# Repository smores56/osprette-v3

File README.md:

The Osprangle
=============

The Osprangle is a slightly modified version of the [Osprette V3][osprette-v3], fit for a rectangular case.
The case in question is from the [Equals 60][equals-60] from Boardsource. The keyboard is a 34-key unibody
that runs on any pro-micro compatible daughterboard. It comes with bluetooth support by way of battery
terminals and a power switch.

# Ordering One

To order one of these from JLC, just upload the `osprangle.zip` archive to the Order Now page at <https://jlcpcb.com>,
and make sure to set a 1.6mm thickness. Removing the order number is always recommended.

# Pictures

_More to come when PCB's arrive!_

[osprette-v3]: https://github.com/smores56/osprette-v3
[equals-60]: https://www.boardsource.xyz/products/equals-60

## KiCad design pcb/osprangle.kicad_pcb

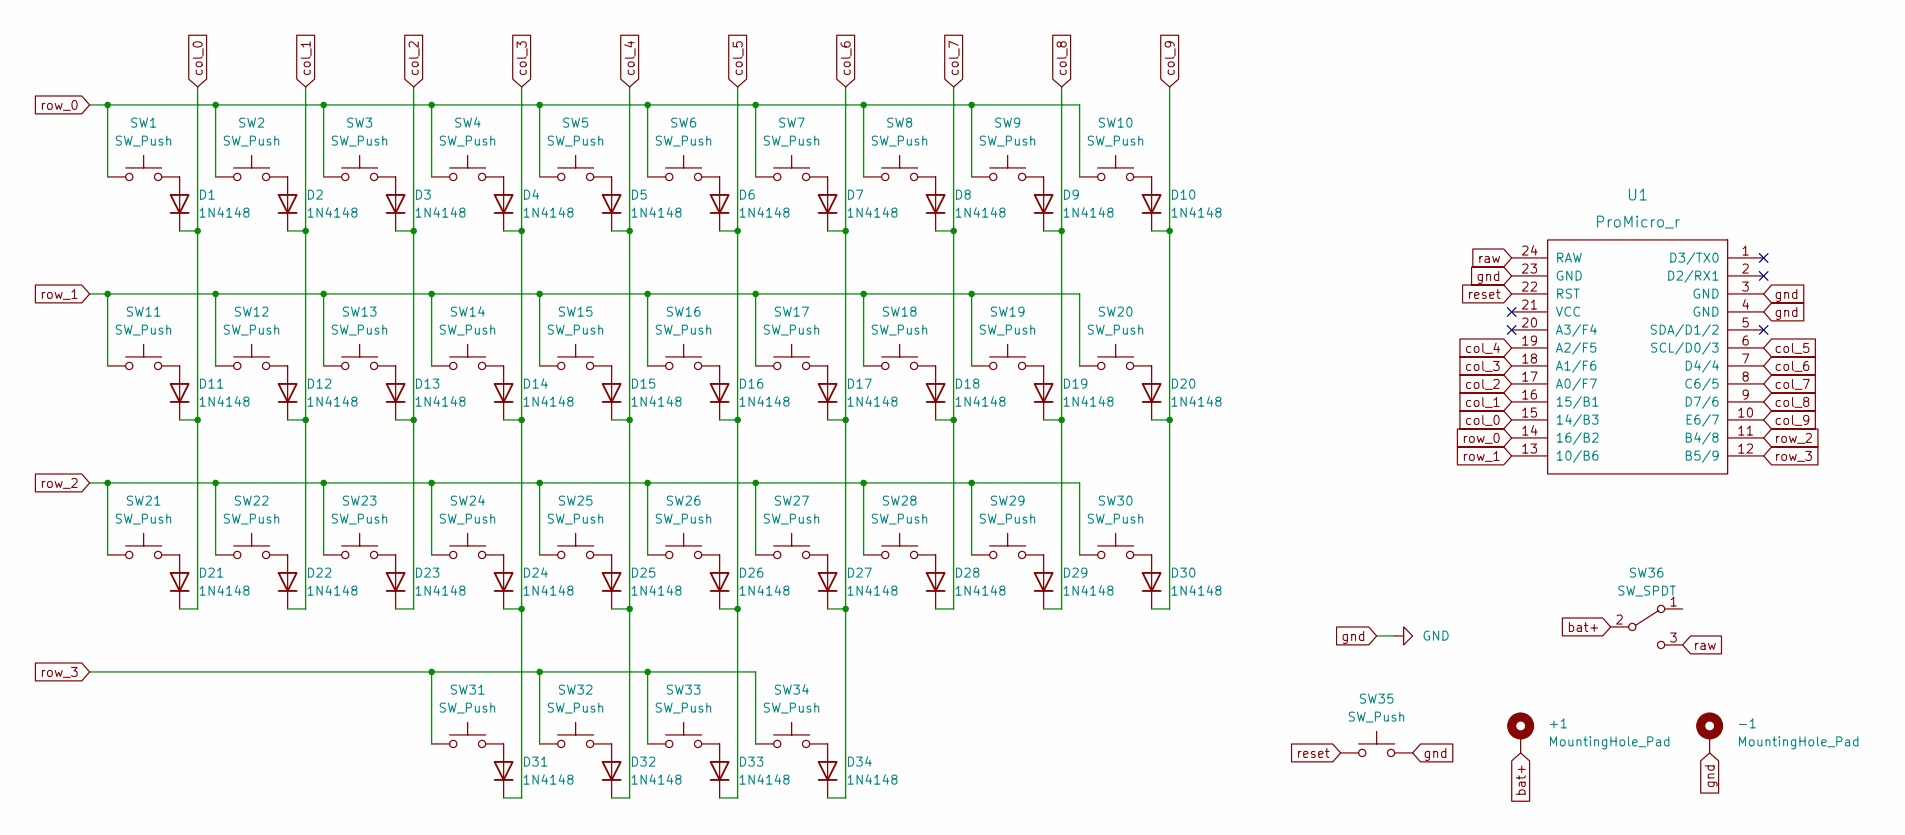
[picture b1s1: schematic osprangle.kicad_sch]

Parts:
+1: MountingHole_Pad; single-pin
-1: MountingHole_Pad; single-pin
D1, D2, D3, D4, D5, D6, D7, D8, D9, D10, D11, D12, D13, D14, D15, D16, D17, D18, D19, D20, D21, D22, D23, D24, D25, D26, D27, D28, D29, D30, D31, D32, D33, D34: 1N4148; smd-diode
SW1, SW2, SW3, SW4, SW5, SW6, SW7, SW8, SW9, SW10, SW11, SW12, SW13, SW14, SW15, SW16, SW17, SW18, SW19, SW20, SW21, SW22, SW23, SW24, SW25, SW26, SW27, SW28, SW29, SW30, SW31, SW32, SW33, SW34: SW_Push; choc-switch-one-sided
SW35: SW_Push; reset-switch-angled-4pin
SW36: SW_SPDT; power-switch
U1: ProMicro_r; pro-micro

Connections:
unnamed: D1.2 (A), SW1.2
unnamed: D2.2 (A), SW2.2
unnamed: D3.2 (A), SW3.2
unnamed: D4.2 (A), SW4.2
unnamed: D5.2 (A), SW5.2
unnamed: D6.2 (A), SW6.2
unnamed: D7.2 (A), SW7.2
unnamed: D8.2 (A), SW8.2
unnamed: D9.2 (A), SW9.2
unnamed: D10.2 (A), SW10.2
unnamed: D11.2 (A), SW11.2
unnamed: D12.2 (A), SW12.2
unnamed: D13.2 (A), SW13.2
unnamed: D14.2 (A), SW14.2
unnamed: D15.2 (A), SW15.2
unnamed: D16.2 (A), SW16.2
unnamed: D17.2 (A), SW17.2
unnamed: D18.2 (A), SW18.2
unnamed: D19.2 (A), SW19.2
unnamed: D20.2 (A), SW20.2
unnamed: D21.2 (A), SW21.2
unnamed: D22.2 (A), SW22.2
unnamed: D23.2 (A), SW23.2
unnamed: D24.2 (A), SW24.2
unnamed: D25.2 (A), SW25.2
unnamed: D26.2 (A), SW26.2
unnamed: D27.2 (A), SW27.2
unnamed: D28.2 (A), SW28.2
unnamed: D29.2 (A), SW29.2
unnamed: D30.2 (A), SW30.2
unnamed: D31.2 (A), SW31.2
unnamed: D32.2 (A), SW32.2
unnamed: D33.2 (A), SW33.2
unnamed: D34.2 (A), SW34.2
bat+: +1.1, SW36.2 (B)
col_0: D1.1 (K), D11.1 (K), D21.1 (K), U1.15 (14/B3)
col_1: D2.1 (K), D12.1 (K), D22.1 (K), U1.16 (15/B1)
col_2: D3.1 (K), D13.1 (K), D23.1 (K), U1.17 (A0/F7)
col_3: D4.1 (K), D14.1 (K), D24.1 (K), D31.1 (K), U1.18 (A1/F6)
col_4: D5.1 (K), D15.1 (K), D25.1 (K), D32.1 (K), U1.19 (A2/F5)
col_5: D6.1 (K), D16.1 (K), D26.1 (K), D33.1 (K), U1.6 (SCL/D0/3)
col_6: D7.1 (K), D17.1 (K), D27.1 (K), D34.1 (K), U1.7 (D4/4)
col_7: D8.1 (K), D18.1 (K), D28.1 (K), U1.8 (C6/5)
col_8: D9.1 (K), D19.1 (K), D29.1 (K), U1.9 (D7/6)
col_9: D10.1 (K), D20.1 (K), D30.1 (K), U1.10 (E6/7)
gnd: -1.1, SW35.2, U1.3 (GND), U1.4 (GND), U1.23 (GND)
raw: SW36.3 (C), U1.24 (RAW)
reset: SW35.1, U1.22 (RST)
row_0: SW1.1, SW2.1, SW3.1, SW4.1, SW5.1, SW6.1, SW7.1, SW8.1, SW9.1, SW10.1, U1.14 (16/B2)
row_1: SW11.1, SW12.1, SW13.1, SW14.1, SW15.1, SW16.1, SW17.1, SW18.1, SW19.1, SW20.1, U1.13 (10/B6)
row_2: SW21.1, SW22.1, SW23.1, SW24.1, SW25.1, SW26.1, SW27.1, SW28.1, SW29.1, SW30.1, U1.11 (B4/8)
row_3: SW31.1, SW32.1, SW33.1, SW34.1, U1.12 (B5/9)

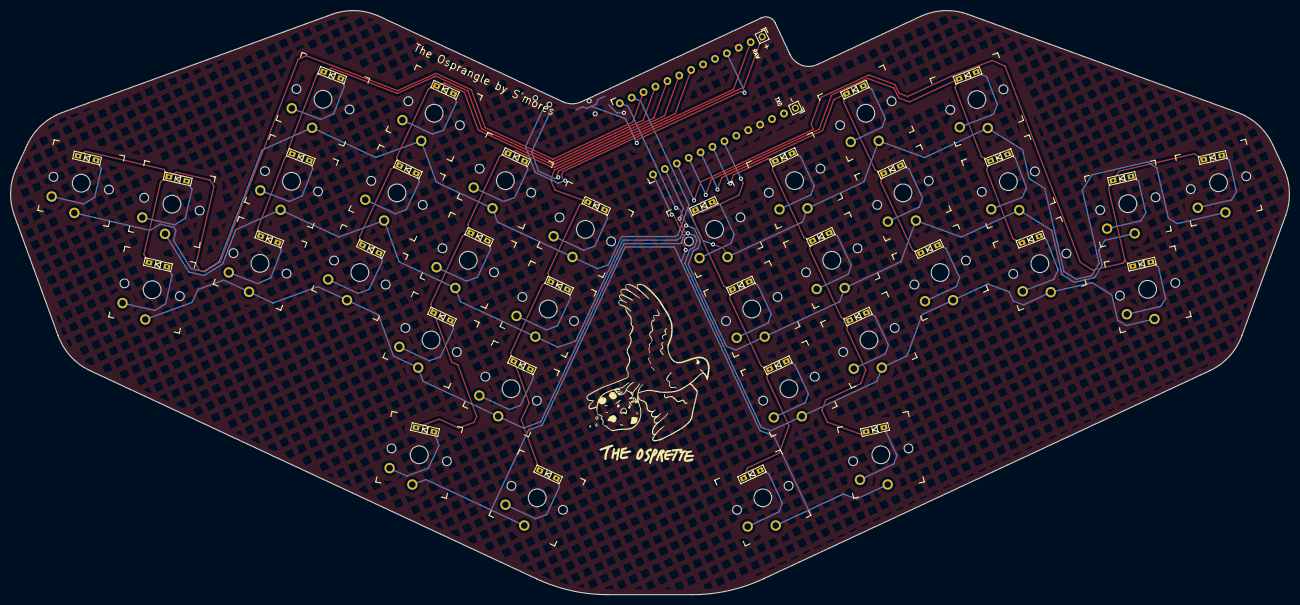
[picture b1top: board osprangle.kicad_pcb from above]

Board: 2 copper layers, 247.3 x 113.0 mm, 73 parts (1 on the bottom side), 52 nets.

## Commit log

2025-05-02 Fix improper forking
